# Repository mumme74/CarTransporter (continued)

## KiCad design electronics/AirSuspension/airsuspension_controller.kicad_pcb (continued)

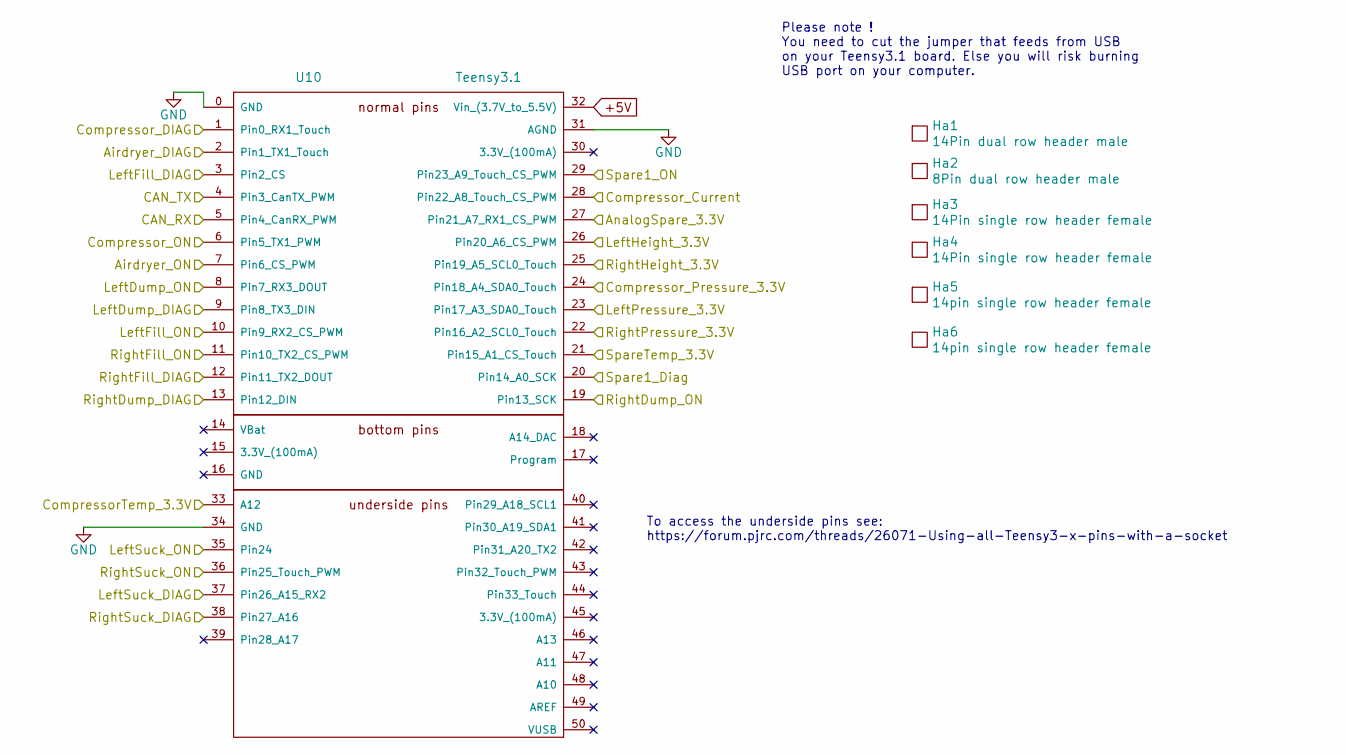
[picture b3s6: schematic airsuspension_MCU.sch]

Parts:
Ha1: 14Pin dual row header male; farnell 2356135
Ha2: 8Pin dual row header male; farnell 2356133
Ha3: 14Pin single row header female; farnell 1667519
Ha4: 14Pin single row header female; part CES-114-01-T-S; farnell 1667519
Ha5, Ha6: 14pin single row header female; farnell 1667519
U10: Teensy3.1; teensy3.1_w_underside; farnell 2430007

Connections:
+5V: U10.32 (Vin_(3.7V_to_5.5V)); also elsewhere on the board
/Airdryer_DIAG: U10.2 (Pin1_TX1_Touch); also elsewhere on the board
/Airdryer_ON: U10.7 (Pin6_CS_PWM); also elsewhere on the board
/AnalogSpare_3.3V: U10.27 (Pin21_A7_RX1_CS_PWM); also elsewhere on the board
/CAN_RX: U10.5 (Pin4_CanRX_PWM); also elsewhere on the board
/CAN_TX: U10.4 (Pin3_CanTX_PWM); also elsewhere on the board
/CompressorCurrent_3.3V: U10.28 (Pin22_A8_Touch_CS_PWM); also elsewhere on the board
/CompressorPressure_3.3V: U10.24 (Pin18_A4_SDA0_Touch); also elsewhere on the board
/CompressorTemp_3.3V: U10.33 (A12); also elsewhere on the board
/Compressor_DIAG: U10.1 (Pin0_RX1_Touch); also elsewhere on the board
/Compressor_ON: U10.6 (Pin5_TX1_PWM); also elsewhere on the board
/LeftDump_DIAG: U10.9 (Pin8_TX3_DIN); also elsewhere on the board
/LeftDump_ON: U10.8 (Pin7_RX3_DOUT); also elsewhere on the board
/LeftFill_DIAG: U10.3 (Pin2_CS); also elsewhere on the board
/LeftFill_ON: U10.10 (Pin9_RX2_CS_PWM); also elsewhere on the board
/LeftHeight_3.3V: U10.26 (Pin20_A6_CS_PWM); also elsewhere on the board
/LeftPressure_3.3V: U10.23 (Pin17_A3_SDA0_Touch); also elsewhere on the board
/LeftSuck_DIAG: U10.37 (Pin26_A15_RX2); also elsewhere on the board
/LeftSuck_ON: U10.35 (Pin24); also elsewhere on the board
/RightDump_DIAG: U10.13 (Pin12_DIN); also elsewhere on the board
/RightDump_ON: U10.19 (Pin13_SCK); also elsewhere on the board
/RightFill_DIAG: U10.12 (Pin11_TX2_DOUT); also elsewhere on the board
/RightFill_ON: U10.11 (Pin10_TX2_CS_PWM); also elsewhere on the board
/RightHeight_3.3V: U10.25 (Pin19_A5_SCL0_Touch); also elsewhere on the board
/RightPressure_3.3V: U10.22 (Pin16_A2_SCL0_Touch); also elsewhere on the board
/RightSuck_DIAG: U10.38 (Pin27_A16); also elsewhere on the board
/RightSuck_ON: U10.36 (Pin25_Touch_PWM); also elsewhere on the board
/Spare1_DIAG: U10.20 (Pin14_A0_SCK); also elsewhere on the board
/Spare1_ON: U10.29 (Pin23_A9_Touch_CS_PWM); also elsewhere on the board
/SpareTemp_3.3V: U10.21 (Pin15_A1_CS_Touch); also elsewhere on the board
GND: U10.0 (GND), U10.31 (AGND), U10.34 (GND); also elsewhere on the board

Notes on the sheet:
Please note ! You need to cut the jumper that feeds from USB on your Teensy3.1 board. Else you will risk burning USB port on your computer.
To access the underside pins see: https://forum.pjrc.com/threads/26071-Using-all-Teensy3-x-pins-with-a-socket

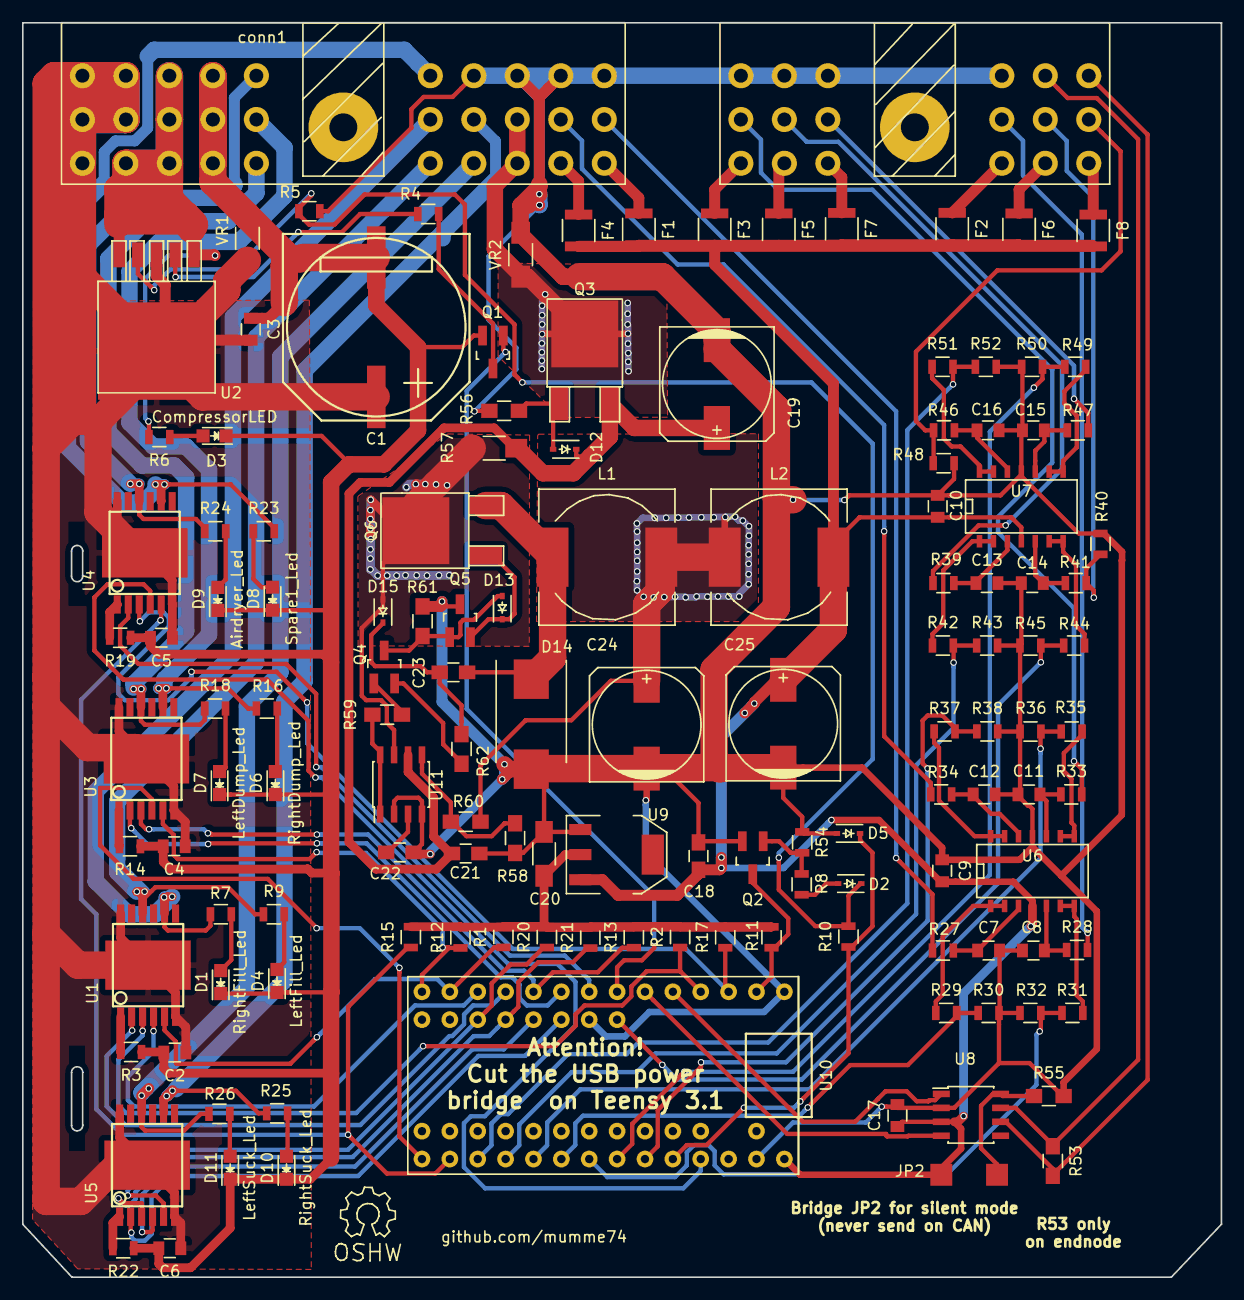
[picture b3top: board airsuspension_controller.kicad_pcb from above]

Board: 2 copper layers, 109.2 x 114.3 mm, 133 parts (0 on the bottom side), 110 nets.

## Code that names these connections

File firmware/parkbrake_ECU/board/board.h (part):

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/*
 * GPIOA setup:
 *
 * PA0  - LeftRear_CS               (analog).
 * PA1  - RightRear_CS              (analog).
 * PA2  - LeftFront_CS              (analog).
 * PA3  - RightFront_CS             (analog).
 * PA4  - LR_speed_in               (input pullup).
 * PA5  - RR_speed_in               (input floating).
 * PA6  - LF_speed_in               (input pullup).
 * PA7  - RF_speed_in               (input pullup).
 * PA8  - LeftRear_DIAG             (input pullup).
 * PA9  - RightRear_DIAG            (input floating).
 * PA10 - PWR_ENABLED_SIG           (input floating).
 * PA11 - CAN_RX                    (alternate 9).
 * PA12 - CAN_TX                    (alternate 9).
 * PA13 - JTMS                      (alternate 0).
 * PA14 - JTCLK                     (alternate 0).
 * PA15 - JTDI                      (alternate 0).
 */
#define VAL_GPIOA_MODER             (PIN_MODE_ANALOG(GPIOA_LeftRear_CS) |   \
                                     PIN_MODE_ANALOG(GPIOA_RightRear_CS) |  \
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/*
 * GPIOB setup:
 *
 * PB0  - PWR_voltsense             (analog).
 * PB1  - LeftFront_DIAG            (input pullup).
 * PB2  - RightFront_DIAG           (input pullup).
 * PB3  - JTDO                      (alternate 0).
 * PB4  - JTNRST                    (alternate 0).
 * PB5  - Bridge_Reset_INV          (output pushpull maximum).
 * PB6  - USART_TX                  (alternate 7).
 * PB7  - USART_RX                  (alternate 7).
 * PB8  - L_speed_out               (output pushpull maximum).
 * PB9  - L_speed_out_inv           (output pushpull maximum).
 * PB10 - PIN10                     (input pullup).
 * PB11 - PIN11                     (input pullup).
 * PB12 - PIN12                     (input pullup).
 * PB13 - PIN13                     (input pullup).
 * PB14 - R_speed_out               (output pushpull maximum).
 * PB15 - R_speed_out_inv           (output pushpull maximum).
 */
#define VAL_GPIOB_MODER             (PIN_MODE_ANALOG(GPIOB_PWR_voltsense) | \
                                     PIN_MODE_INPUT(GPIOB_LeftFront_DIAG) | \
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/*
 * GPIOC setup:
 *
 * PC0  - Feed_voltsense            (analog).
 * PC1  - INDICATOR_ON              (output opendrain minimum).
 * PC2  - LeftFront_Tighten         (output opendrain maximum).
 * PC3  - LeftFront_Loosen          (output opendrain maximum).
 * PC4  - RightFront_Tighten        (output pushpull maximum).
 * PC5  - RightFront_Loosen         (output pushpull maximum).
 * PC6  - SPI_CS                    (alternate 5).
 * PC7  - SPI_SCK                   (alternate 5).
 * PC8  - SPI_MISO                  (alternate 5).
 * PC9  - SPI_MOSI                  (alternate 5).
 * PC10 - LeftRear_Tighten          (output pushpull maximum).
 * PC11 - LeftRear_Loosen           (output pushpull maximum).
 * PC12 - RightRear_Tighten         (output pushpull maximum).
 * PC13 - RightRear_Loosen          (output pushpull maximum).
 * PC14 - uC_SET_POWER              (output pushpull maximum).
 * PC15 - VR_diag_test              (output pushpull minimum).
 */
#define VAL_GPIOC_MODER             (PIN_MODE_ANALOG(GPIOC_Feed_voltsense) |\
                                     PIN_MODE_OUTPUT(GPIOC_INDICATOR_ON) |  \
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 *
 * PD0  - PIN0                      (alternate 7).
 * PD1  - PIN1                      (alternate 7).
 * PD2  - IGN_ON_SIG                (input pulldown).
 * PD3  - PIN3                      (alternate 7).
 * PD4  - PIN4                      (alternate 7).
 * PD5  - PIN5                      (alternate 7).
 * PD6  - PIN6                      (alternate 7).
 * PD7  - PIN7                      (input pullup).
 * PD8  - LIGHTS_ON_SIG             (input pulldown).
 * PD9  - PIN9                      (input pullup).
 * PD10 - PIN10                     (input pullup).
 * PD11 - PIN11                     (output pushpull maximum).
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 * PE5  - PIN5                      (input pullup).
 * PE6  - PIN6                      (input pulldown).
 * PE7  - PIN7                      (analog).
 * PE8  - BUTTON_SIG                (input pulldown).
 * PE9  - BUTTON_INV_SIG            (input pullup).
 * PE10 - PIN10                     (input pullup).
 * PE11 - PIN11                     (input pullup).
 * PE12 - PIN12                     (input pullup).
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/*
 * GPIOF setup:
 *
 * PF0  - OSC_IN                    (input floating).
 * PF1  - OSC_OUT                   (input floating).
 * PF2  - PIN2                      (input pulldown).
 * PF3  - PIN3                      (input pullup).
 * PF4  - PIN4                      (input pulldown).
 * PF5  - PIN5                      (input pullup).
 * PF6  - TIGHTEN_CMD_SIG           (input pullup).
 * PF7  - RELEASE_CMD_SIG           (input pulldown).
 * PF8  - PIN8                      (input pullup).
 * PF9  - PIN9                      (input pulldown).
 * PF10 - PIN10                     (input pulldown).
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
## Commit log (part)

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2013-01-07 *untested*, first attempt
2013-01-07 Share spi bus for multiple peripherals
2013-01-07 add some notice
2013-01-09 refactor
2013-01-09 Add configurable options
2013-01-09 refactor code with API changes, update readme.
2013-01-10 do cleanup on duplicates
2013-01-10 api change.
2013-01-10 update debug checks
2015-03-15 Initial commit Only Airsuspension ECU schematic for now
2015-04-07 Firmware and some changes in electronics schema
2015-04-07 implemnt some weight calculation code based on pressure sensors
2015-04-08 HeightController commands from CAn implemented
2015-04-19 First live test on a teensy ifxed some bugs that hanged initialization
2015-04-19 Some more fottprints added to PCB
2015-05-17 Some more footprints and beginning PCB work
2016-03-29 Add a few forgotten files
2016-03-29 Changed to a more stable powersupply (3Amps 5V and separate 3.3v) + some few cleanups due to updated kicad
2016-03-31 First placement with a ModICE enclosure
2016-04-02 Some updates as some parts were not available
2016-04-03 first checkin of parkbrake module
2016-04-04 Fixes to Bat switch and polarity protection
2016-04-17 Add currentlimit latching to avaoid current limit oscilation Start a mcu schema part
2016-07-17 Changed value of load sensing resistor for 5V switch do reduce system noise
2016-07-21 More work on parkbrake node
2016-07-21 Added warning
2016-07-21 ordernr, type and footprints for all components
2016-07-21 Make it pass DRC rule check
2016-07-22 More fixes and chenged components eat less boardspace
2016-07-28 more work on parkbrake ecu Rear H-bridge more or less finished
2016-07-28 Front motors H-bridge finished
2016-08-02 More work on inputs and 5 volt
2016-08-04 traceroute finished although there probably is some errors
2016-08-04 Component ids moved and removed silkscreen for high current copper, solder strengthed copper
2016-08-05 Added copperareas
2017-01-03 Changed solder trace zones, was silkscreen now soldermask
2017-01-08 Some updates
2017-01-08 Spelling
2017-01-08 Some helper files
2017-01-08 Updated installation diagram files
2017-07-25 Some changes to suspension
2017-07-25 Initial commit starting a chibios firmware for parkbrake
2017-07-25 Dont follow eclipse specific files/folders
2017-07-27 More work, added control logic for motors and a settings interface Also switched eeprom lib
2017-07-28 More changes to parkbrake, added logic for controling button and refined motor activation logic
2017-07-31 Changed debug out to a separate file started Implement CAN Tried to make wheelsensors measurement work (not in a working state yet)
2017-07-31 Added Antilock functionality, also added settings changable through can
2017-07-31 More work on CAN, PID updates implemented
2017-08-04 Compile fix
2017-08-04 More work on the diag interface via CAN bus Should be more or less feature complete now -> wheelspeeds info require pcb re-engineering
2017-08-06 Beginning raspberry3 displaynode
2017-08-06 More work on GUI
2017-08-07 Made header useable by displaynode too, need enum
2017-08-07 More work on CAN->C++->QML bridge DTC and freezeFrames should work now
2017-08-08 Activation parkbrake node works Also some work on user exceptions from parkbrakenode
2017-08-08 Add support for settings and error notifications
2017-08-08 trying to make a install script
2017-08-13 More changes to start stupport suspension node
2017-08-13 Bug fix and unify can protocol
2017-08-13 More work integrating suspensionnode into displaynode
2018-03-30 Refactoring, share code via baseclass
2018-03-30 quelsh some warnings
2018-03-31 More changes to to make activate functionanlity for suspensionNode
2018-03-31 More functionality around suspensionNode activation
2018-04-01 Parameters more or less finished
2018-04-01 Housekeeping, cleanup
2018-04-01 Compile fix on macOS
2018-04-01 DTC fixes for suspensionNode
2018-04-02 Added sensor reverse to suspensionNode config and some more bugfixes
2018-04-02 Diagnose and settings feature complete now
2018-04-02 documentation
2018-04-02 added a response to height changes
2018-04-02 Height status changes added, error messages when we cant send to CAN and many small bug fixes
2018-04-07 Added more functionality frontpage dialogs
2018-04-08 cleanup, erased dead code
2018-04-08 Make diagnosticpages swipe-able
2018-04-08 Bugfix DTC parkbrake erase button of screen Enhanched weight dialog
2018-04-08 Added swedish translations Made translations work with macos and win
2018-04-08 added a simple clock widget
2018-04-08 Pedantic
2018-07-11 Changes to documentation
2018-07-11 Cleanup and start a clock widget
2018-07-12 Removed old lib, is included in teensyduino now
2018-07-12 Fix crash on real hardware, beginning bughunt
2018-07-12 Bugfixes for NTC, pressure and CAN
2018-07-13 Bugfixes height adjustment and settingsbox in qml
2018-07-13 Simplyfy API and avoid frames sent on wrong type
2018-07-13 Added a CAN error table to ui
2018-07-13 Added functionality to quit app through keyboard Ctrl+C
2018-07-13 Turn of debug DTCs
2018-07-13 many fixes to make CAN work more consistently with displaynode
2018-07-13 Fixes to make displayNode work consitently with suspensionNode
2018-07-14 Added DTC listmodel to be in C++, solves DTC triggering on the fly
2018-07-16 Many more bugfixes
2018-07-18 Many bugfixes, for example make height statemachine work Re-engineer to exclude Compressor pwm controlled to relay control
2018-07-18 minor tweaks to pcb, had a cap on wrong polarity
2018-07-18 Fix compiler warnings when build -O0
2018-07-20 minor tweaks
2018-07-20 Make asm compiler aware of C debug flags
2018-07-20 Update conf files to latest standard
2018-07-20 Mailbox buffers was not initialized properly by chMBObjectInit created kernel panic
2018-07-20 reduce switching noise from 5v regulator circuit
2018-07-21 Fix display of volts
2018-07-21 Tweak CAN inputs on board config
2018-07-21 Make sensors working
2018-07-21 Make CAN baudrate 250000 and fix some bugs in RPC mechanism
2018-07-21 More bugfixes diag and control modules
2018-07-21 unconst settings, was stored in ROM so my implementation did'nt have chance of working
2018-07-21 Attempt to make eeprom save nonblock to rx thread
2018-07-22 Made EEPROM work
2018-07-22 Made DTC working
2018-07-22 Many tweaks to can rpc mechanism
2018-07-22 temporary bypass input flags during debugging process
2018-07-22 Wrong IC
2018-07-22 Struggle with chibios events, not yet sorted it out
2018-07-23 Try with a volatile shared variable
2018-07-23 Make parkbrake activation activate correct wheel
2018-07-23 More tries with events, now with multiple listeners Chibios events are hard to grasp :(
2018-07-24 Made ADC bridge work somewhat very hard on processortime
2018-07-25 Added Serial over CAN, started adopting candump to be a tool for CAN serial during debug
2018-07-25 Adapt commandline inputs for canserial to match our needs
2018-07-25 Cleanup
2018-07-26 Added serial debugprint through CAN on suspensionNode also
2018-07-26 Made canserial.c based on BaseSequentialStream
2018-07-26 Soften cpu usage
2018-07-26 Tweaks to motorcurrents measurement
2018-07-26 Fix hang due to lost variable after thd switch
2018-07-26 Rethink hardware current limit, it didn't work as I rememberd
2018-07-28 Made a bootloader app, uses libopencm3
2018-07-29 Made a bootloader application to run on raspberrypi (in terminal) Not yet complete and definetly not debugged
2018-07-29 Spelling errors
2018-07-30 Commenting code, minor fixes and spelling
2018-07-31 Changes to the bootloader app
2018-07-31 Forgot these
2018-07-31 Cleanup IDEs user files
2018-07-31 Hide IDE user files from git
2018-08-01 Made read memory, checksums, memoryinfo and canfilters work
2018-08-02 Change bootloader offset (startingpoint)
2018-08-07 Got a bit further, it saves a memorypage onto flash now, bails out on consequtive mempage
2018-08-11 More work, still ha a race condition and loosing frames
2018-08-11 Reimplemented a recieve-send with a fifo (queue) and copy memory, not shared storage
2018-08-11 Struggled all day to make queued can pages to work It can recieve a bin from node to host now
2018-08-12 write bin to node works (sort of, not yet debuged extensively)
2018-08-12 Fix problem with bin of odd size fail on write Fix problem with jump to application Fix bootloadermode hook when a valid bin is in flash (can filter problem)
2019-07-02 Starting to port bootloader to teensy3
2019-07-02 added reference for consistency
2019-07-03 Broke out some common functions to a architecture common file
2019-07-03 Added peek to fifo
2019-07-03 Made bootloader node feature complete for teensy, untested though
2019-07-03 tweak gitignore
2019-07-03 Tweak ld script, did hang due read access violation.
2019-07-05 First attempt to abstract driver, eventually be able to use different drivers and port to macos and windows
2019-07-05 Tweaked drivers choice
2019-07-05 Begin new driver slcan (can over serialport ala lawicell)
2019-07-05 Porting changes, endianess
2019-07-06 More work on slcan driver
2019-07-06 Better fault description when serial send errors
2019-07-06 API consistency
2019-07-06 Activate slcan driver and apple fixes
2019-07-06 Remove fixme comments
2019-07-07 Add baud speed settings, needed for slcan
2019-07-07 Speed changes and more work on slcan
2019-07-07 Refactor cli interface
2019-07-07 Latency issues with FTDI chips
2019-07-07 Implemented a buffer on the response side
2019-07-08 Reduce function count
2019-07-08 Redo the response fetch buffer, can now handle asyncronous responses
2019-07-08 Speeling fixes
2019-07-08 Tweak help description
2019-07-09 Bugfixes CAN send and recieve
2019-07-09 Linux fixes
2019-07-09 Compiler warnings, clock issue
2019-07-09 Warning in schematic
2019-07-09 Safer error reporting
2019-07-09 Portability
2019-07-10 Arduino makefile fixes for linux machine
2019-07-10 Continue chasing can I/O bugs
2019-07-10 Windows compile issues
2019-07-10 More windows fixes, got a bit further
2019-07-11 I think slan <-> canusb mostly works by now. More work on teensy node code
2019-07-12 Fix bug reset, reduce binzize and simplify debug printing
2019-07-12 Begin to move to c only app (reduce bin size)
2019-07-13 A CAN driver standalone from FlexCAN lib
2019-07-13 Got FlexCAN to send and recieve, same loss of frame though
2019-07-14 Fix bug on ID field, fix reset
2019-07-14 Working read commandgit add . -u
2019-07-14 Got host software o work on reads
2019-07-14 Last frame was off by 1
2019-07-15 Read and writes work on network level. Still issues with alignment in node code for teensy
2019-07-15 Fixed a error on read when requesting non aligned(uint32_t) size Fixed issue with writing to both block of a flash section
2019-07-15 Changed BOOTLOADER_PAGE_SIZE to be more intuitive
2019-07-16 Added filter option
2019-07-16 Git exclude *.bin files
2019-07-17 Fix a bug in write to node Tried to activate CAN filter
2019-07-18 Fixes to make suspension work with bootloader
2019-07-18 Changes to make host app for bootloader sync with bootloader firmware
2019-07-18 Finally won a long struggle to make bootloader jump to application
2019-07-18 Windows changes, compiles but still apear to have some timing issues
2019-07-19 Got the windows port to work. Tested with both USBTin and lawicell canusb
2019-07-19 Reverse order prolonged bootloader time if DEBUG_PRINT
2019-07-19 Fix lost frame issue
2019-07-20 Made read from serial be more informative and it works on macos now
2019-07-20 Enhanced bootmode
2019-07-20 Made can send big endian, easier to read in candump
2019-07-20 introduce delay to make slow interfaces work even in socketcan mode
2019-07-20 Syncronous serial prots is such a PITA This time its windows
2019-07-20 More work on bootmode
2019-07-21 Port parkbrakenode to Chibios 19 (HAL7 and Chibi6)
2019-07-22 Moved macro to functions, saved some space
2019-07-22 Routed together control and pwm modules
2019-07-22 Tried to centralize byte shuffling unions to one file rename canframe_t -> can_frame_t to avoid name clash
2019-07-22 Squelsh some semantic warnings in qtcreator
2019-07-23 Added a sanity check for uploading bins
2019-07-23 got a bit further with filters in nodes
2019-07-23 Stm32 filter issues solved and some other bugs ironed out
2019-07-24 Added a Raminfo command
